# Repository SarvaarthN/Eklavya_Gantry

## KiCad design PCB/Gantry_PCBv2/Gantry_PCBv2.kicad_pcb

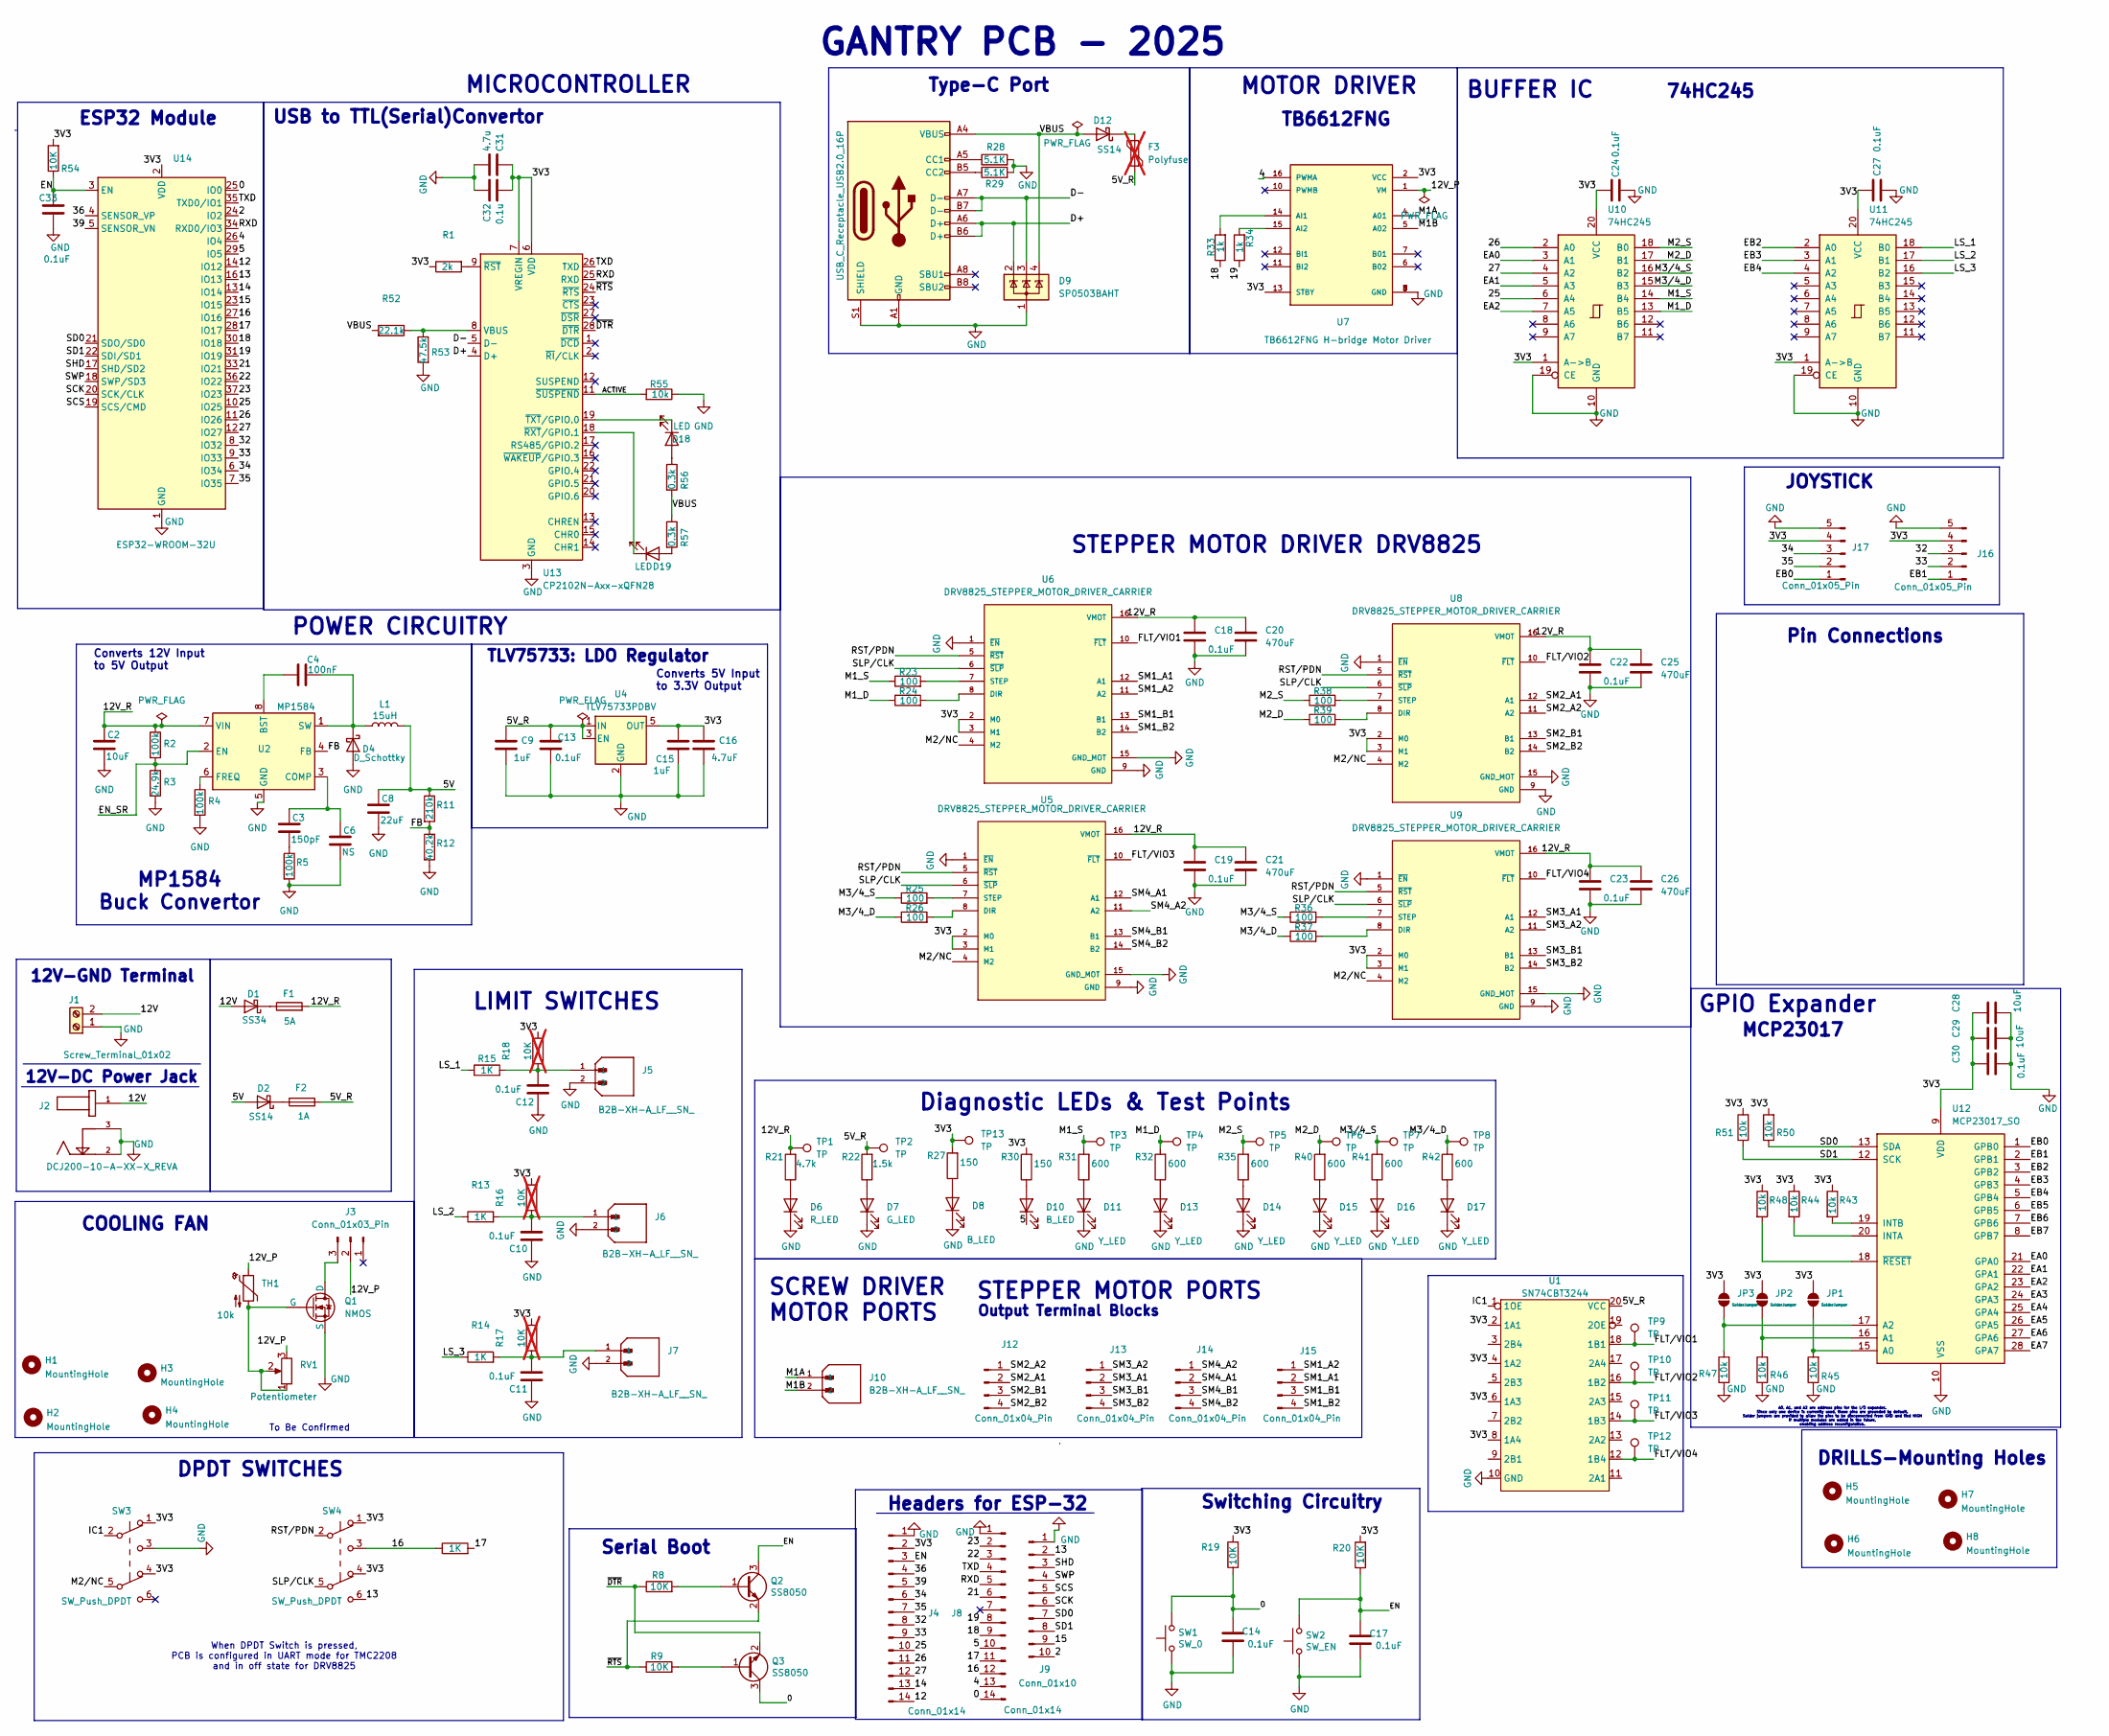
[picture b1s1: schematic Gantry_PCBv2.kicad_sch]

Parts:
C2, C28, C29: 10uF; C_0805_2012Metric_Pad1.18x1.45mm_HandSolder
C3: 150pF; C_0805_2012Metric_Pad1.18x1.45mm_HandSolder
C4: 100nF; C_0805_2012Metric_Pad1.18x1.45mm_HandSolder
C6: NS; C_0805_2012Metric_Pad1.18x1.45mm_HandSolder
C8: 22uF; C_0805_2012Metric_Pad1.18x1.45mm_HandSolder
C9, C15: 1uF; C_0805_2012Metric_Pad1.18x1.45mm_HandSolder
C10, C11, C12, C13, C14, C17, C18, C19, C22, C23, C24, C27, C30, C33: 0.1uF; C_0805_2012Metric_Pad1.18x1.45mm_HandSolder
C16: 4.7uF; C_0805_2012Metric_Pad1.18x1.45mm_HandSolder
C20, C21, C25, C26: 470uF; CP_Elec_10x10.5
C31: 4.7u; C_0805_2012Metric_Pad1.18x1.45mm_HandSolder
C32: 0.1u; C_0805_2012Metric_Pad1.18x1.45mm_HandSolder
D1: SS34; D_SMB
D2, D12: SS14; D_SMA
D4: D_Schottky; D_SMA_Handsoldering
D6: R_LED; LED_0805_2012Metric_Pad1.15x1.40mm_HandSolder
D7: G_LED; LED_0805_2012Metric_Pad1.15x1.40mm_HandSolder
D8, D10: B_LED; LED_0805_2012Metric_Pad1.15x1.40mm_HandSolder
D9: SP0503BAHT; SOT-143
D11, D13, D14, D15, D16, D17: Y_LED; LED_0805_2012Metric_Pad1.15x1.40mm_HandSolder
D18, D19: LED; LED_0805_2012Metric_Pad1.15x1.40mm_HandSolder
F1: 5A; Fuse_Littelfuse-LVR100
F2: 1A; Fuse_Littelfuse-LVR100
F3: Polyfuse; Fuse_Littelfuse-LVR100; not fitted
H1, H2, H3, H4, H5, H6, H7, H8: MountingHole; MountingHole_3.2mm_M3
J1: Screw_Terminal_01x02; TerminalBlock_bornier-2_P5.08mm
J2: DCJ200-10-A-XX-X_REVA; BarrelJack_GCT_DCJ200-10-A_Horizontal
J3: Conn_01x03_Pin; JST_EH_B3B-EH-A_1x03_P2.50mm_Vertical
J4, J8: Conn_01x14; PinHeader_1x14_P2.54mm_Vertical
J5, J6, J7, J10: B2B-XH-A_LF__SN_; JST_EH_B2B-EH-A_1x02_P2.50mm_Vertical; PARTREV N/A
J9: Conn_01x10; PinHeader_1x10_P2.54mm_Vertical
J11: USB_C_Receptacle_USB2.0_16P; USB_C_Receptacle_GCT_USB4105-xx-A_16P_TopMnt_Horizontal
J12, J13, J14, J15: Conn_01x04_Pin; JST_EH_B4B-EH-A_1x04_P2.50mm_Vertical
J16, J17: Conn_01x05_Pin; PinHeader_1x05_P2.54mm_Vertical
JP1, JP2, JP3: SolderJumper; SolderJumper-3_P1.3mm_Open_Pad1.0x1.5mm_NumberLabels
L1: 15uH; L_Sunlord_MWSA0603S
Q1: NMOS; TO-247-3_Vertical
Q2, Q3: SS8050; SOT-23
R1: 2k; R_0805_2012Metric_Pad1.20x1.40mm_HandSolder
R2, R4, R5: 100k; R_0805_2012Metric_Pad1.20x1.40mm_HandSolder
R3: 24.9k; R_0805_2012Metric_Pad1.20x1.40mm_HandSolder
R8, R9, R19, R20, R54: 10K; R_0805_2012Metric_Pad1.20x1.40mm_HandSolder
R11: 210k; R_0805_2012Metric_Pad1.20x1.40mm_HandSolder
R12: 40.2k; R_0805_2012Metric_Pad1.20x1.40mm_HandSolder
R13, R14, R15, R49: 1K; R_0805_2012Metric_Pad1.20x1.40mm_HandSolder
R16, R17, R18: 10K; R_0805_2012Metric_Pad1.20x1.40mm_HandSolder; not fitted
R21: 4.7k; R_0805_2012Metric_Pad1.20x1.40mm_HandSolder
R22: 1.5k; R_0805_2012Metric_Pad1.20x1.40mm_HandSolder
R23, R24, R25, R26, R36, R37, R38, R39: 100; R_0805_2012Metric_Pad1.20x1.40mm_HandSolder
R27, R30: 150; R_0805_2012Metric_Pad1.20x1.40mm_HandSolder
R28, R29: 5.1K; R_0805_2012Metric_Pad1.20x1.40mm_HandSolder
R31, R32, R35, R40, R41, R42: 600; R_0805_2012Metric_Pad1.20x1.40mm_HandSolder
R33, R34: 1k; R_0805_2012Metric_Pad1.20x1.40mm_HandSolder
R43, R44, R45, R46, R47, R48, R50, R51, R55: 10k; R_0805_2012Metric_Pad1.20x1.40mm_HandSolder
R52: 22.1k; R_0805_2012Metric_Pad1.20x1.40mm_HandSolder
R53: 47.5k; R_0805_2012Metric_Pad1.20x1.40mm_HandSolder
R56, R57: 0.3k; R_0805_2012Metric_Pad1.20x1.40mm_HandSolder
RV1: Potentiometer; Potentiometer_Bourns_3266Y_Vertical
SW1: SW_0; SW_Push_SPST_NO_Alps_SKRK
SW2: SW_EN; SW_Push_SPST_NO_Alps_SKRK
SW3, SW4: SW_Push_DPDT; dpdt
TH1: 10k; R_0805_2012Metric_Pad1.20x1.40mm_HandSolder
TP1, TP2, TP3, TP4, TP5, TP6, TP7, TP8, TP9, TP10, TP11, TP12, TP13: TP; TestPoint_Pad_D2.0mm
U1: SN74CBT3244; TSSOP-20_4.4x5mm_P0.5mm
U2: MP1584; SOIC-8-1EP_3.9x4.9mm_P1.27mm_EP2.41x3.3mm
U4: TLV75733PDBV; SOT-23-5
U5, U6, U8, U9: DRV8825_STEPPER_MOTOR_DRIVER_CARRIER; stepper
U7: TB6612FNG H-bridge Motor Driver; MODULE_ROB-14450
U10, U11: 74HC245; SOIC-20W_7.5x15.4mm_P1.27mm
U12: MCP23017_SO; SOIC-28W_7.5x17.9mm_P1.27mm
U13: CP2102N-Axx-xQFN28; QFN-28-1EP_5x5mm_P0.5mm_EP3.35x3.35mm
U14: ESP32-WROOM-32U

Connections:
/0: C14.2, J8.14, Q3.3, R19.1, SW1.2, U14.25 (IO0)
/2: J9.10, U14.24 (IO2)
/3V3: C15.1, C16.1, C24.2, C27.2, C28.1, C29.1, C30.1, C31.1, C32.2, J4.2, J16.4, J17.4, JP1.2 (B), JP2.2 (B), JP3.2 (B), R1.1, R16.2, R17.2, R18.2, R19.2, R20.2, R27.2, R30.2, R43.1, R44.1, R48.1, R50.2, R51.2, R54.2, SW3.1 (A), SW3.4 (A), SW4.1 (A), SW4.4 (A), TP13.1, U1.2 (1A1), U1.4 (1A2), U1.6 (1A3), U1.8 (1A4), U4.5 (OUT), U5.2 (M0), U5.3 (M1), U6.2 (M0), U6.3 (M1), U7.2 (VCC), U7.13 (STBY), U8.2 (M0), U8.3 (M1), U9.2 (M0), U9.3 (M1), U10.1 (A->B), U10.20 (VCC), U11.1 (A->B), U11.20 (VCC), U12.9 (VDD), U13.6 (VDD), U13.7 (VREGIN), U14.2 (VDD); also elsewhere on the board
/4: J8.13, U7.16 (PWMA), U14.26 (IO4)
/5: D10.1 (K), J8.10, U14.29 (IO5)
/5V: C8.1, D2.2 (A), L1.2, R11.1
/5V_R: C9.1, C13.1, F2.2, F3.1, R22.2, TP2.1, U1.20 (VCC), U4.1 (IN), U4.3 (EN); also elsewhere on the board
/12: J4.14, U14.14 (IO12)
/12V: D1.2 (A), J1.2, J2.1
/12V_P: J3.2, RV1.3, TH1.1, U7.1 (VM)
/12V_R: C2.1, C18.1, C19.1, C20.1, C21.1, C22.1, C23.1, C25.1, C26.1, F1.2, R2.1, R21.2, TP1.1, U2.7 (VIN), U5.16 (VMOT), U6.16 (VMOT), U8.16 (VMOT), U9.16 (VMOT); also elsewhere on the board
/13: J9.2, SW4.6 (C), U14.16 (IO13)
/14: J4.13, U14.13 (IO14)
/15: J9.9, U14.23 (IO15)
/16: J8.12, R49.1, SW4.3 (C), U14.27 (IO16)
/17: J8.11, R49.2, U14.28 (IO17)
/18: J8.9, R33.1, U14.30 (IO18)
/19: J8.8, R34.1, U14.31 (IO19)
/21: J8.6, U14.33 (IO21)
/22: J8.3, U14.36 (IO22)
/23: J8.2, U14.37 (IO23)
/25: J4.10, U10.6 (A4), U14.10 (IO25)
/26: J4.11, U10.2 (A0), U14.11 (IO26)
/27: J4.12, U10.4 (A2), U14.12 (IO27)
/32: J4.8, J16.3, U14.8 (IO32)
/33: J4.9, J16.2, U14.9 (IO33)
/34: J4.6, J17.3, U14.6 (IO34)
/35: J4.7, J17.2, U14.7 (IO35)
/36: J4.4, U14.4 (SENSOR_VP)
/39: J4.5, U14.5 (SENSOR_VN)
/ACTIVE: R55.2, U13.11 (~SUSPEND)
/D+: D9.2 (K), J11.A6 (D+), J11.B6 (D+), U13.4 (D+)
/D-: D9.3 (K), J11.A7 (D-), J11.B7 (D-), U13.5 (D-)
/EA0: U10.3 (A1), U12.21 (GPA0)
/EA1: U10.5 (A3), U12.22 (GPA1)
/EA2: U10.7 (A5), U12.23 (GPA2)
/EA3: U12.24 (GPA3)
/EA4: U12.25 (GPA4)
/EA5: U12.26 (GPA5)
/EA6: U12.27 (GPA6)
/EA7: U12.28 (GPA7)
/EB0: J17.1, U12.1 (GPB0)
/EB1: J16.1, U12.2 (GPB1)
/EB2: U11.2 (A0), U12.3 (GPB2)
/EB3: U11.3 (A1), U12.4 (GPB3)
/EB4: U11.4 (A2), U12.5 (GPB4)
/EB5: U12.6 (GPB5)
/EB6: U12.7 (GPB6)
/EB7: U12.8 (GPB7)
/EN: C17.2, C33.1, J4.3, Q2.3, R20.1, R54.1, SW2.2, U14.3 (EN)
/EN_SR: R2.2, R3.1, U2.2 (EN)
/FB: R11.2, R12.1, U2.4 (FB)
/FLT/VIO1: TP9.1, U1.18 (1B1), U6.10 (~FLT); also elsewhere on the board
/FLT/VIO2: TP10.1, U1.16 (1B2), U8.10 (~FLT); also elsewhere on the board
/FLT/VIO3: TP11.1, U1.14 (1B3), U5.10 (~FLT); also elsewhere on the board
/FLT/VIO4: TP12.1, U1.12 (1B4), U9.10 (~FLT); also elsewhere on the board
/IC1: SW3.2 (B), U1.1 (1OE)
/LS_1: R15.1, U11.18 (B0)
/LS_2: R13.1, U11.17 (B1)
/LS_3: R14.1, U11.16 (B2)
/M1A: J10.1, U7.4 (A01)
/M1B: J10.2, U7.5 (A02)
/M1_D: R24.1, R32.2, TP4.1, U10.13 (B5); also elsewhere on the board
/M1_S: R23.1, R31.2, TP3.1, U10.14 (B4); also elsewhere on the board
/M2_D: R39.1, R40.2, TP6.1, U10.17 (B1); also elsewhere on the board
/M2_S: R35.2, R38.1, TP5.1, U10.18 (B0); also elsewhere on the board
/M2/NC: SW3.5 (B), U5.4 (M2), U6.4 (M2), U8.4 (M2), U9.4 (M2)
/M3/4_D: R26.1, R37.1, R42.2, TP8.1, U10.15 (B3); also elsewhere on the board
/M3/4_S: R25.1, R36.1, R41.2, TP7.1, U10.16 (B2); also elsewhere on the board
/RST/PDN: SW4.2 (B), U5.5 (~RST), U6.5 (~RST), U8.5 (~RST), U9.5 (~RST)
/RXD: J8.5, U13.25 (RXD), U14.34 (RXD0/IO3)
/SCK: J9.6, U14.20 (SCK/CLK)
/SCS: J9.5, U14.19 (SCS/CMD)
/SD0: J9.7, R50.1, U12.13 (SDA), U14.21 (SDO/SD0)
/SD1: J9.8, R51.1, U12.12 (SCK), U14.22 (SDI/SD1)
/SHD: J9.3, U14.17 (SHD/SD2)
/SLP/CLK: SW4.5 (B), U5.6 (~SLP), U6.6 (~SLP), U8.6 (~SLP), U9.6 (~SLP)
/SM1_A1: J15.2, U6.12 (A1)
/SM1_A2: J15.1, U6.11 (A2)
/SM1_B1: J15.3, U6.13 (B1)
/SM1_B2: J15.4, U6.14 (B2)
/SM2_A1: J12.2, U8.12 (A1)
/SM2_A2: J12.1, U8.11 (A2)
/SM2_B1: J12.3, U8.13 (B1)
/SM2_B2: J12.4, U8.14 (B2)
/SM3_A1: J13.2, U9.12 (A1)
/SM3_A2: J13.1, U9.11 (A2)
/SM3_B1: J13.3, U9.13 (B1)
/SM3_B2: J13.4, U9.14 (B2)
/SM4_A1: J14.2, U5.12 (A1)
/SM4_A2: J14.1, U5.11 (A2)
/SM4_B1: J14.3, U5.13 (B1)
/SM4_B2: J14.4, U5.14 (B2)
/SWP: J9.4, U14.18 (SWP/SD3)
/TXD: J8.4, U13.26 (TXD), U14.35 (TXD0/IO1)
/VBUS: D9.4 (K), D12.2 (A), J11.A4 (VBUS), J11.A9 (VBUS), J11.B4 (VBUS), J11.B9 (VBUS), R52.2, R56.2, R57.1
/~DTR: Q3.2, R8.1, U13.28 (~DTR)
/~RTS: Q2.2, R9.1, U13.24 (~RTS)
GND: C2.2, C6.2, C8.2, C9.2, C10.2, C11.2, C12.2, C13.2, C14.1, C15.2, C16.2, C17.1, C18.2, C19.2, C20.2, C21.2, C22.2, C23.2, C24.1, C25.2, C26.2, C27.1, C28.2, C29.2, C30.2, C31.2, C32.1, C33.2, D4.2 (A), D6.1 (K), D7.1 (K), D8.1 (K), D9.1 (A), D11.1 (K), D13.1 (K), D14.1 (K), D15.1 (K), D16.1 (K), D17.1 (K), J1.1, J2.2, J2.3, J4.1, J5.2, J6.2, J7.2, J8.1, J9.1, J11.A1 (GND), J11.A12 (GND), J11.B1 (GND), J11.B12 (GND), J11.S1 (SHIELD), J16.5, J17.5, Q1.3 (S), R3.2, R4.2, R5.2, R12.2, R28.2, R29.2, R45.1, R46.1, R47.1, R53.2, R55.1, SW1.1, SW2.1, SW3.3 (C), U1.10 (GND), U2.5 (GND), U4.2 (GND), U5.1 (~EN), U5.9 (GND), U5.15 (GND_MOT), U6.1 (~EN), U6.9 (GND), U6.15 (GND_MOT), U7.3 (GND), U7.8 (GND), U7.9 (GND), U8.1 (~EN), U8.9 (GND), U8.15 (GND_MOT), U9.1 (~EN), U9.9 (GND), U9.15 (GND_MOT), U10.10 (GND), U10.19 (CE), U11.10 (GND), U11.19 (CE), U12.10 (VSS), U13.3 (GND), U13.29 (GND), U14.1 (GND), U14.15 (GND), U14.38 (GND), U14.39 (GND)
unnamed: C3.2, R5.1
unnamed: C10.1, J6.1, R13.2, R16.1
unnamed: C11.1, J7.1, R14.2, R17.1
unnamed: C12.1, J5.1, R15.2, R18.1
unnamed: D1.1 (K), F1.1
unnamed: D2.1 (K), F2.1
unnamed: C4.2, D4.1 (K), L1.1, U2.1 (SW)
unnamed: D6.2 (A), R21.1
unnamed: D7.2 (A), R22.1
unnamed: D8.2 (A), R27.1
unnamed: D10.2 (A), R30.1
unnamed: D11.2 (A), R31.1
unnamed: D12.1 (K), F3.2
unnamed: D13.2 (A), R32.1
unnamed: D14.2 (A), R35.1
unnamed: D15.2 (A), R40.1
unnamed: D16.2 (A), R41.1
unnamed: D17.2 (A), R42.1
unnamed: D18.2 (A), R56.1
unnamed: D18.1 (K), U13.19 (~TXT/GPIO.0)
unnamed: D19.2 (A), R57.2
unnamed: D19.1 (K), U13.18 (~RXT/GPIO.1)
unnamed: J3.3, Q1.1 (D)
unnamed: J11.A5 (CC1), R28.1
unnamed: J11.B5 (CC2), R29.1
unnamed: JP1.1 (A), R45.2, U12.15 (A0)
unnamed: JP2.1 (A), R46.2, U12.16 (A1)
unnamed: JP3.1 (A), R47.2, U12.17 (A2)
unnamed: Q1.2 (G), RV1.1, RV1.2, TH1.2
unnamed: Q2.1, R8.2
unnamed: Q3.1, R9.2
unnamed: C4.1, U2.8 (BST)
unnamed: C3.1, C6.1, U2.3 (COMP)
unnamed: R4.1, U2.6 (FREQ)
unnamed: R26.2, U5.8 (DIR)
unnamed: R25.2, U5.7 (STEP)
unnamed: R24.2, U6.8 (DIR)
unnamed: R23.2, U6.7 (STEP)
unnamed: R33.2, U7.14 (AI1)
unnamed: R34.2, U7.15 (AI2)
unnamed: R39.2, U8.8 (DIR)
unnamed: R38.2, U8.7 (STEP)
unnamed: R37.2, U9.8 (DIR)
unnamed: R36.2, U9.7 (STEP)
unnamed: R44.2, U12.20 (INTA)
unnamed: R43.2, U12.19 (INTB)
unnamed: R48.2, U12.18 (~RESET)
unnamed: R52.1, R53.1, U13.8 (VBUS)
unnamed: R1.2, U13.9 (~RST)

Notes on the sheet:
STEPPER MOTOR PORTS
GANTRY PCB - 2025
12V-GND Terminal
STEPPER MOTOR DRIVER DRV8825
ESP32 Module
Serial Boot
Converts 12V Input to 5V Output
Converts 5V Input to 3.3V Output
Output Terminal Blocks
MCP23017
DRILLS-Mounting Holes
Type-C Port
74HC245
COOLING FAN
Diagnostic LEDs & Test Points
MICROCONTROLLER
Pin Connections
POWER CIRCUITRY
12V-DC Power Jack
TLV75733: LDO Regulator
To Be Confirmed
GPIO Expander
LIMIT SWITCHES
BUFFER IC
MP1584 Buck Convertor
JOYSTICK
When DPDT Switch is pressed, PCB is configured in UART mode for TMC2208 and in off state for DRV8825
Headers for ESP-32
A0, A1, and A2 are address pins for the I/O expander. Since only one device is currently used, these pins are grounded by default. Solder jumpers are provided to allow the pins to be disconnected from GND and tied HIGH if multiple modules are added in the future, enabling address reconfiguration.
DPDT SWITCHES
MOTOR DRIVER
SCREW DRIVER MOTOR PORTS
Switching Circuitry
USB to TTL(Serial)Convertor
TB6612FNG

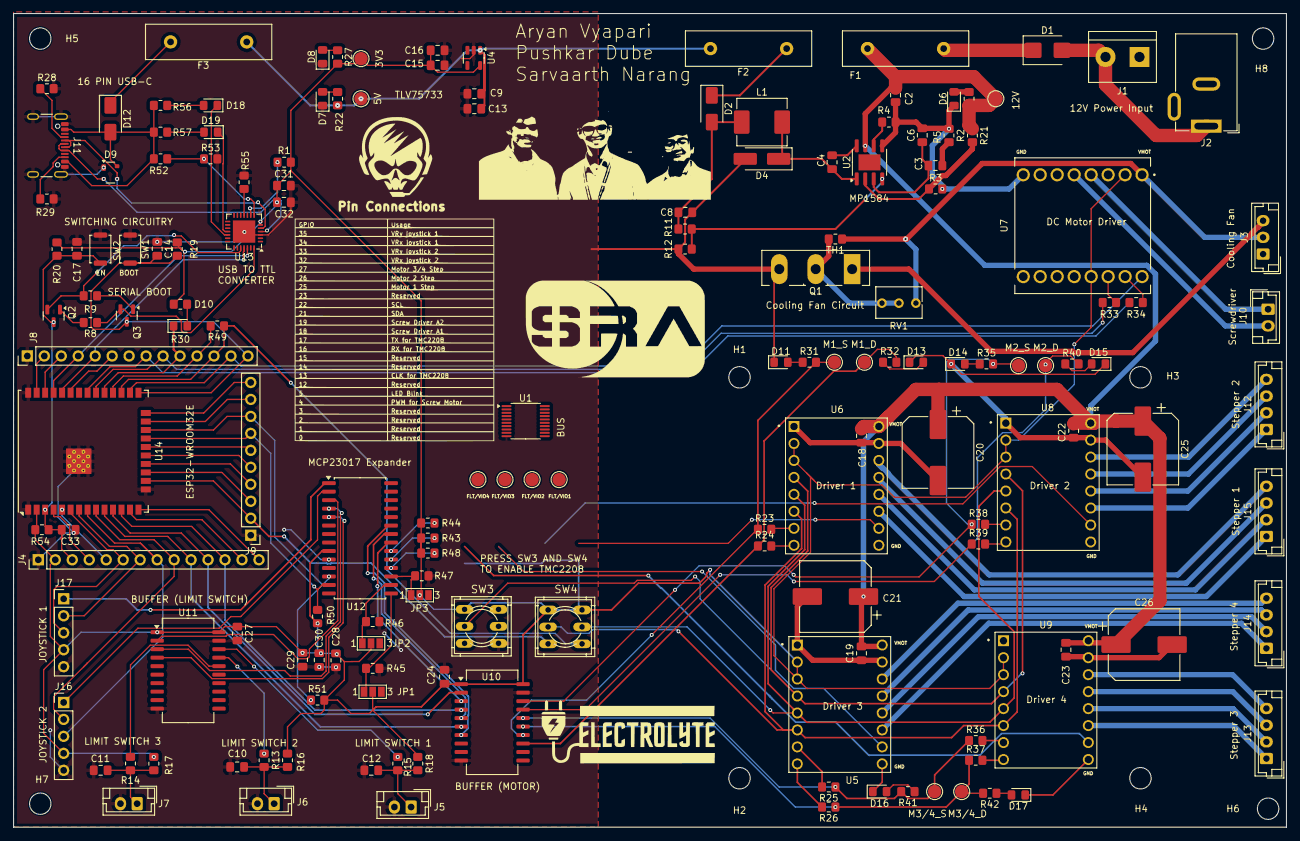
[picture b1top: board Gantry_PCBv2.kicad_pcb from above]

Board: 2 copper layers, 190.5 x 121.8 mm, 168 parts (0 on the bottom side), 140 nets.

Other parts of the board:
3V3, 5V, 12V: TP; TestPoint_Pad_D2.0mm
FLT/VIO1, FLT/VIO2, FLT/VIO3, FLT/VIO4: TP; TestPoint_Pad_D2.0mm
M1_D, M1_S, M2_D, M2_S, M3/4_D, M3/4_S: TP; TestPoint_Pad_D2.0mm

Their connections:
/3V3: 3V3.1; also elsewhere on the board
/5V_R: 5V.1; also elsewhere on the board
/12V_R: 12V.1; also elsewhere on the board
/FLT/VIO1: FLT/VIO1.1; also elsewhere on the board
/FLT/VIO2: FLT/VIO2.1; also elsewhere on the board
/FLT/VIO3: FLT/VIO3.1; also elsewhere on the board
/FLT/VIO4: FLT/VIO4.1; also elsewhere on the board
/M1_D: M1_D.1; also elsewhere on the board
/M1_S: M1_S.1; also elsewhere on the board
/M2_D: M2_D.1; also elsewhere on the board
/M2_S: M2_S.1; also elsewhere on the board
/M3/4_D: M3/4_D.1; also elsewhere on the board
/M3/4_S: M3/4_S.1; also elsewhere on the board

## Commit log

2025-09-27 Added basic uart testing code
2025-10-14 first draft of uart microstepping
2025-12-29 PCB continuation
2025-12-29 complete PCB without silkscreen
2025-12-30 final PCB Rounting without silkscreen
2026-01-03 Schematic v3
2026-01-04 Initital Implementation of Library for DRV8825
2026-01-04 Added Comments
2026-01-19 Initital implmentation for gpio expander MCP23017
2026-01-22 Expander Debug and TMC incorporation
2026-02-01 Added Stepper Motor Driver and DPDT switches Footprints
2026-02-03 fixing errors in schematic
2026-02-09 gantry PCB routing first draft
2026-02-10 Routing 2nd Draft
2026-02-11 Layout Updated
2026-02-16 Another iteration
2026-02-24 Added Labels to parts whose positions are confirmed
2026-02-24 Adding zaxis code
2026-02-25 Added Octal Bus Symbol
2026-02-26 Final symbol for Switch Bus
2026-03-02 Completed Bus Schematic, Added Labels and Rounded the Tracks
2026-03-02 Finished routing for BUS IC, yet to solve DRC issues
2026-03-03 Update Gantry PCBv2 layout and cleanup temp files
2026-03-04 controlled motor using joystick
2026-03-13 updated .gitignore
2026-03-15 Added Silkscreen
2026-03-16 FINAL ITERATION OF PCB, silkscreen complete
2026-03-16 Added Gerber Files
2026-03-18 correct PCB branch
